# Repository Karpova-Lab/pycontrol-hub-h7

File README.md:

- [Documentation](https://karpova-lab.github.io/pycontrol-hub-h7/)
- [Development discussion](https://github.com/orgs/pyControl/discussions/171)

# pyControl Hub H7

A high-performance hardware hub for [pyControl](https://pycontrol.readthedocs.io/en/latest/), built around an [STM32H743VIT6](https://www.digikey.com/short/4cmvhp93) microcontroller. It interfaces with pyControl [devices](https://pycontrol.readthedocs.io/en/latest/user-guide/hardware/#devices) to record inputs and control outputs for behavioral experiments.

## Features

- 480 MHz Cortex-M7, 1 MB RAM, 2 MB external QSPI flash
- 11 pyControl behavior ports
  - 10 RJ45 connectors
  - 1 auxiliary [8-position terminal block](https://www.digikey.com/short/fpqf2rj0) that pairs with a [screw terminal plug](https://www.digikey.com/short/n57m4m7h)
- 2 BNC connectors
- 1 I²C connector compatible with [Qwiic](https://www.sparkfun.com/qwiic) / [STEMMA QT](https://learn.adafruit.com/introducing-adafruit-stemma-qt/what-is-stemma-qt) / [Qw/ST](https://shop.pimoroni.com/en-us/collections/breakouts?tags=Qw/ST) / [Modulino](https://store.arduino.cc/collections/modulino)
- USB Type-C connector with ESD protection
- DC barrel jack input with reverse polarity protection
- On/off toggle switch, 4 user buttons, reset button, and a DFU button for bootloader access
- Power and USB indicator LEDs, plus 4 user-controllable LEDs (red, yellow, green, blue)
- [Metal enclosure](https://karpova-lab.github.io/pycontrol-hub-h7/building/#case)
- Mounting holes compatible with [DIN rail adapters](https://www.digikey.com/short/h7977mfv) for securing to a [DIN rail](https://www.digikey.com/en/products/filter/hardware-fasteners-accessories/580?s=N4IgjCBcpgHAzFUBjKAzAhgGwM4FMAaEAeygG0QAWMeWSgThAF0iAHAFyhAGV2AnAJYA7AOYgAvkQC0AJiQhUkfgFdCJciACszcZJBzIFACIBJAHIACPhgFYQRU5eu2dQA). Alternatively, the case can sit on [rubber feet](https://www.mcmaster.com/9377k311/).

See the [board comparison](https://karpova-lab.github.io/pycontrol-hub-h7/#pycontrol-board-comparison) for how it stacks up against the pyControl Breakout 1.2.

## Photos

## Peripherals and pin mapping

## Schematic

## Repository layout

| Path | Contents |
|------|----------|
| [`ecad/`](ecad) | KiCad schematic and PCB, BOMs, and Gerbers |
| [`mcad/`](mcad) | Enclosure (laser-cut panels, STEP models) and 3D-printed standoffs |
| [`zensical/`](zensical) | Documentation source |
| [`docs/`](docs) | Built documentation site, served by GitHub Pages |

The KiCad libraries in `ecad/libs` are a git submodule, so clone recursively:

```sh
git clone --recursive https://github.com/Karpova-Lab/pycontrol-hub-h7.git
```

## License

- Hardware designs: [Janelia Open-Source Hardware license](LICENSE_HW.txt)
- Software: [BSD 3-Clause license](LICENSE_SW.txt)

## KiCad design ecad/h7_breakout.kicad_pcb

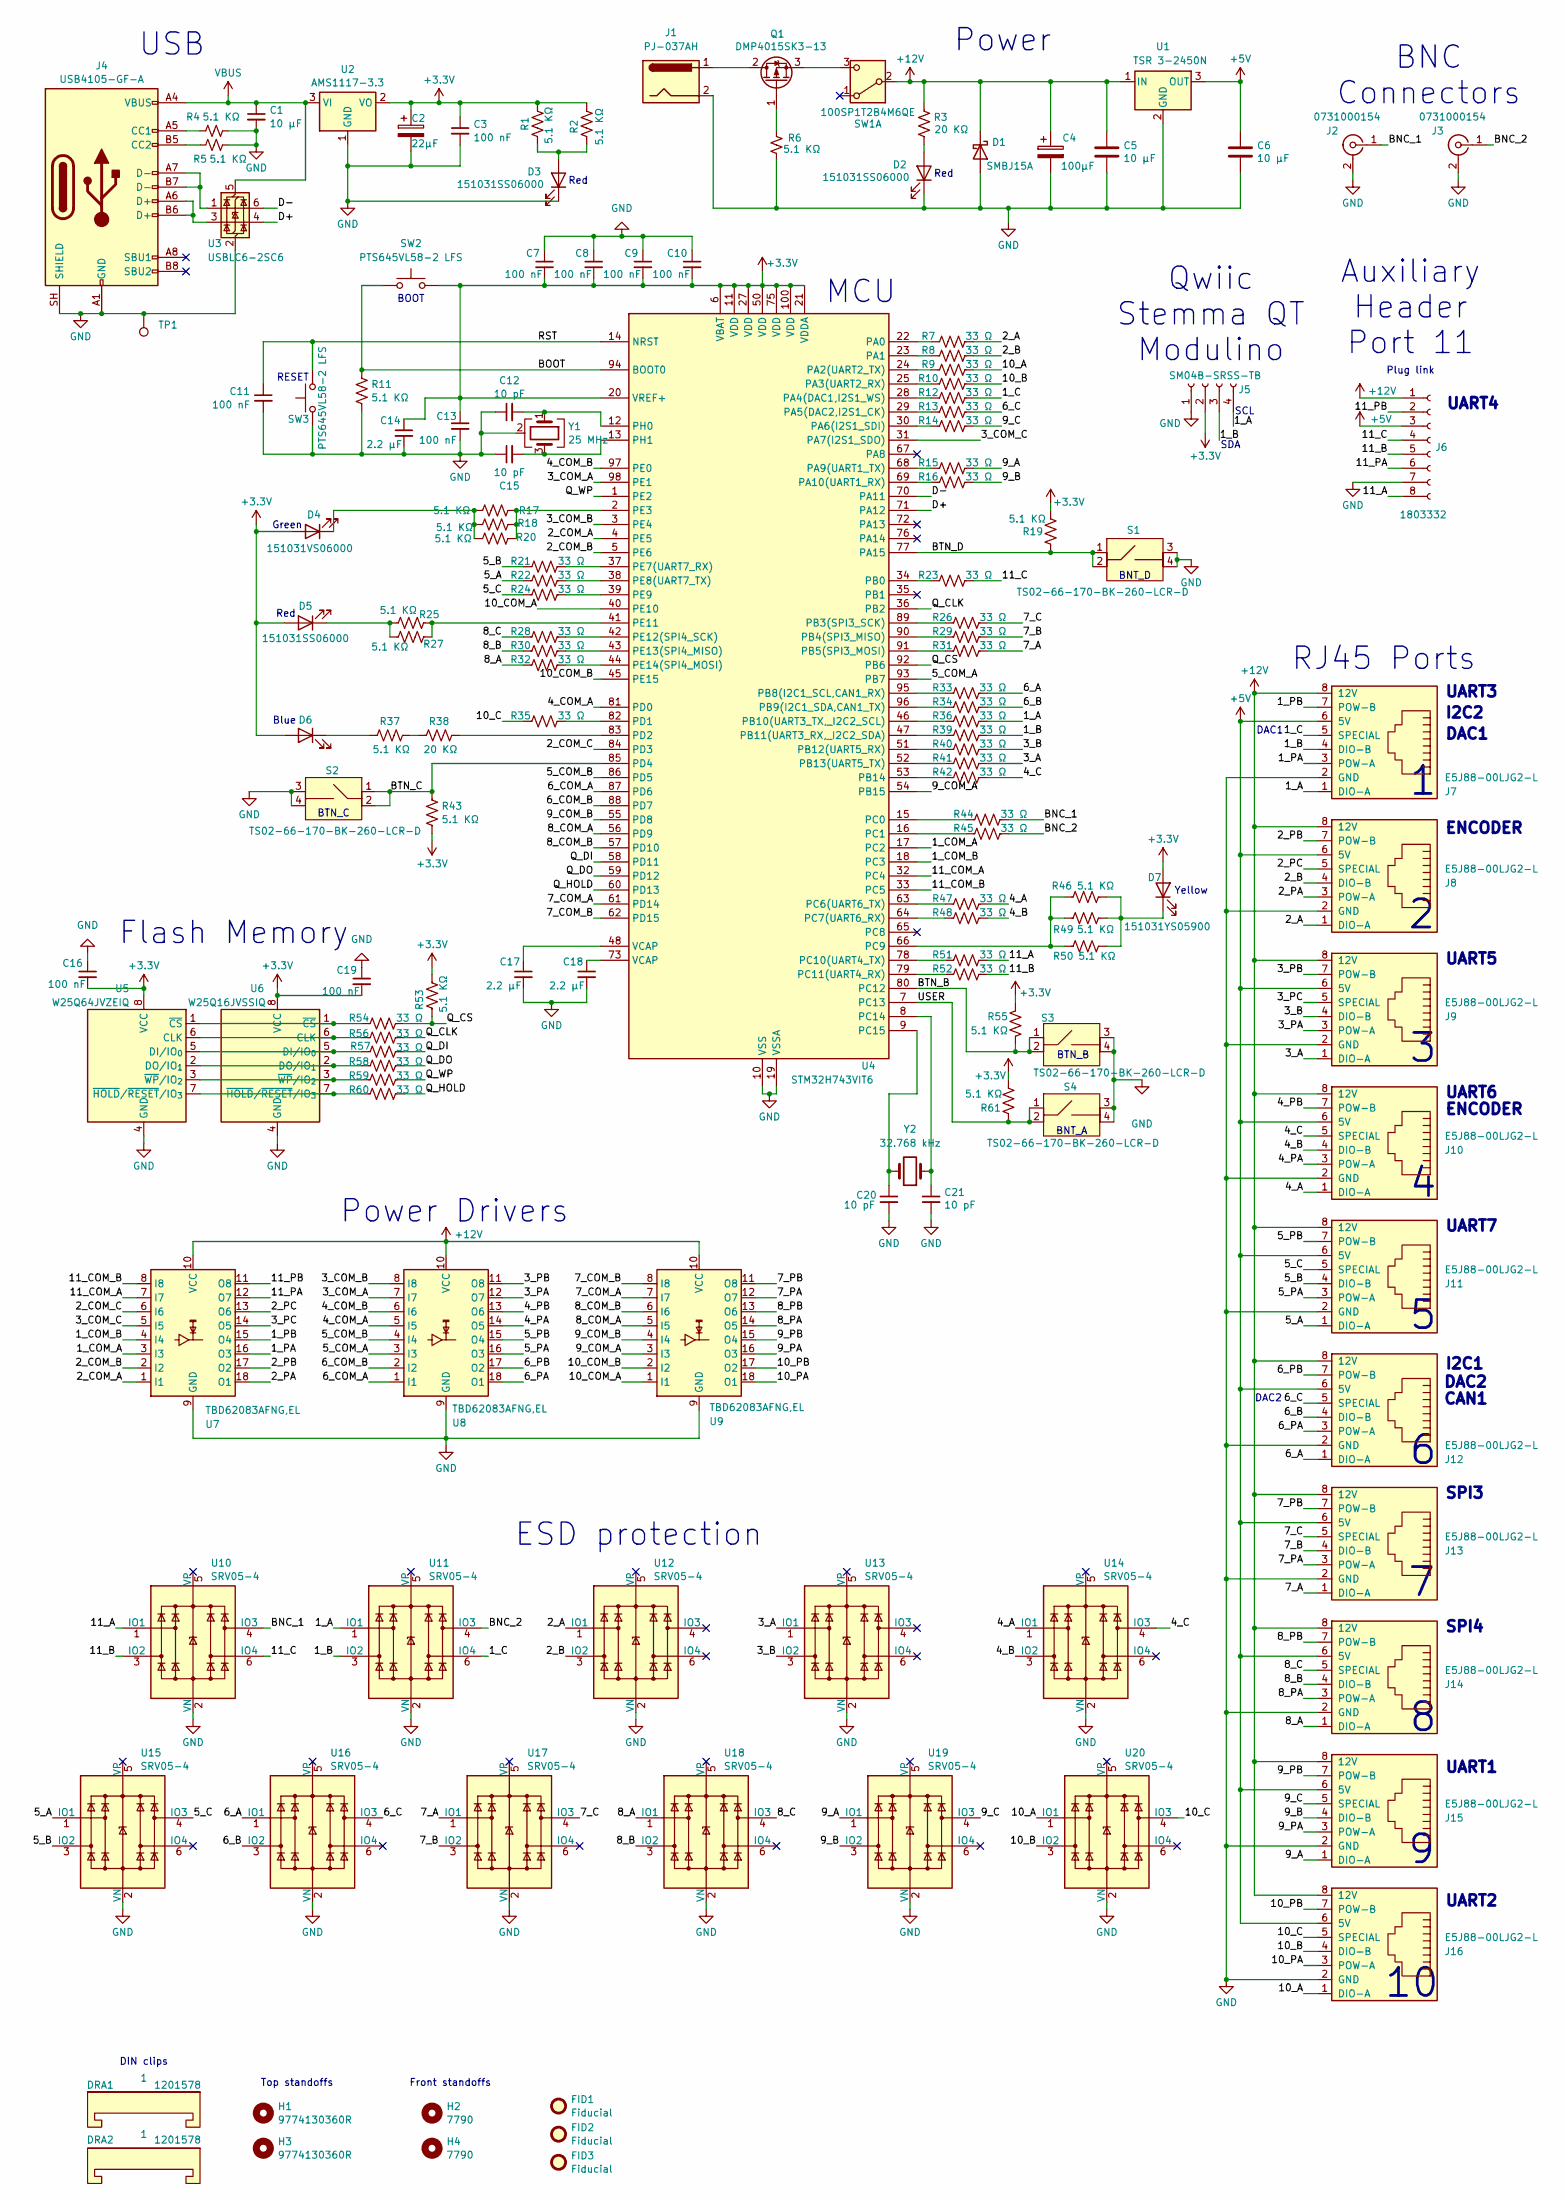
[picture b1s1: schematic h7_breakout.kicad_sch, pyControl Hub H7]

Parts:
C1, C5, C6: 10 µF; C_1206_3216Metric_Pad1.33x1.80mm_HandSolder
C2: 22µF; CP_EIA-3528-21_Kemet-B_HandSolder
C3, C7, C8, C9, C10, C11, C13, C16, C19: 100 nF; C_0603_1608Metric_Pad1.08x0.95mm_HandSolder
C4: 100µF; C_Elec_8x10.2
C12, C15, C20, C21: 10 pF; C_0603_1608Metric_Pad1.08x0.95mm_HandSolder
C14, C17, C18: 2.2 µF; C_0603_1608Metric_Pad1.08x0.95mm_HandSolder
D1: SMBJ15A; D_SMB
D2, D3, D5: 151031SS06000; LED_D3.0mm
D4: 151031VS06000; LED_D3.0mm
D6: 151033BS03000; LED_D3.0mm
D7: 151031YS05900; LED_D3.0mm
DRA1, DRA2: 1201578; DIN_Clip
FID1, FID2, FID3: Fiducial; Fiducial_0.75mm_Mask2.25mm
H1, H3: 9774130360R; standoff_13mm
H2, H4: 7790; RA_screw_mount
J1: PJ-037AH; DC_Jack
J2, J3: 0731000154; BNC RA Jack
J4: USB4105-GF-A; USB_C_Receptacle_GCT_USB4105-xx-A_16P_TopMnt_Horizontal
J5: SM04B-SRSS-TB; JST_SH_SM04B-SRSS-TB_1x04-1MP_P1.00mm_Horizontal
J6: 1803332; PhoenixContact_MC_1,5_8-G-3.81_1x08_P3.81mm_Horizontal
J7, J8, J9, J10, J11, J12, J13, J14, J15, J16: E5J88-00LJG2-L; RJ45_THP_tab_on_top
Q1: DMP4015SK3-13; TO-252-2
R1, R2, R4, R5, R6, R11, R17, R18, R19, R20, R25, R27, R37, R43, R46, R49, R50, R53, R55, R61: 5.1 KΩ; R_0603_1608Metric_Pad0.98x0.95mm_HandSolder
R3, R38: 20 KΩ; R_0603_1608Metric_Pad0.98x0.95mm_HandSolder
R7, R8, R9, R10, R12, R13, R14, R15, R16, R21, R22, R23, R24, R26, R28, R29, R30, R31, R32, R33, R34, R35, R36, R39, R40, R41, R42, R44, R45, R47, R48, R51, R52, R54, R56, R57, R58, R59, R60: 33 Ω; R_0603_1608Metric_Pad0.98x0.95mm_HandSolder
S1, S2, S3, S4: TS02-66-170-BK-260-LCR-D; SW_TH_Tactile_TS02-66-170
SW1: 100SP1T2B4M6QE; RA toggle
SW2, SW3: PTS645VL58-2 LFS; SW_Tactile_SPST_Angled_PTS645Vx58-2LFS
TP1: TestPoint_THTPad_D2.0mm_Drill1.0mm
U1: TSR 3-2450N; Converter_DCDC_traco_3A
U2: AMS1117-3.3; SOT-223-3_TabPin2
U3: USBLC6-2SC6; SOT-23-6; LCSC C7519
U4: STM32H743VIT6; LQFP-100_14x14mm_P0.5mm; LCSC C114409
U5: W25Q64JVZEIQ; WSON-8-1EP_8x6mm_P1.27mm_EP3.4x4.3mm; LCSC C97522
U6: W25Q16JVSSIQ; SOIC-8_5.3x5.3mm_P1.27mm
U7, U8, U9: TBD62083AFNG,EL; SSOP-18_4.4x6.5mm_P0.65mm; LCSC C163229
U10, U11, U12, U13, U14, U15, U16, U17, U18, U19, U20: SRV05-4; SOT-23-6; LCSC C460588
Y1: 25 MHz; crystal_STDCRS2-25M
Y2: 32.768 kHz; Crystal_SMD_EuroQuartz_EQ161-2Pin_3.2x1.5mm_HandSoldering

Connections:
+5V: C6.1, J6.3, J7.6 (5V), J8.6 (5V), J9.6 (5V), J10.6 (5V), J11.6 (5V), J12.6 (5V), J13.6 (5V), J14.6 (5V), J15.6 (5V), J16.6 (5V), U1.3 (OUT)
+12V: C4.1, C5.1, D1.1 (K), J6.1, J7.8 (12V), J8.8 (12V), J9.8 (12V), J10.8 (12V), J11.8 (12V), J12.8 (12V), J13.8 (12V), J14.8 (12V), J15.8 (12V), J16.8 (12V), R3.1, SW1.2 (B), U1.1 (IN), U7.10 (VCC), U8.10 (VCC), U9.10 (VCC)
/1_A: J5.4, J7.1 (DIO-A), R36.2, U11.1 (IO1)
/1_B: J5.3, J7.4 (DIO-B), R39.2, U11.3 (IO2)
/1_C: J7.5 (SPECIAL), R12.2, U11.6 (IO4)
/1_COM_A: U4.17 (PC2), U7.3 (I3)
/1_COM_B: U4.18 (PC3), U7.4 (I4)
/1_PA: J7.3 (POW-A), U7.16 (O3)
/1_PB: J7.7 (POW-B), U7.15 (O4)
/2_A: J8.1 (DIO-A), R7.2, U12.1 (IO1)
/2_B: J8.4 (DIO-B), R8.2, U12.3 (IO2)
/2_COM_A: U4.4 (PE5), U7.1 (I1)
/2_COM_B: U4.5 (PE6), U7.2 (I2)
/2_COM_C: U4.84 (PD3), U7.6 (I6)
/2_PA: J8.3 (POW-A), U7.18 (O1)
/2_PB: J8.7 (POW-B), U7.17 (O2)
/2_PC: J8.5 (SPECIAL), U7.13 (O6)
/3_A: J9.1 (DIO-A), R41.2, U13.1 (IO1)
/3_B: J9.4 (DIO-B), R40.2, U13.3 (IO2)
/3_COM_A: U4.98 (PE1), U8.7 (I7)
/3_COM_B: U4.3 (PE4), U8.8 (I8)
/3_COM_C: U4.31 (PA7(I2S1_SDO)), U7.5 (I5)
/3_PA: J9.3 (POW-A), U8.12 (O7)
/3_PB: J9.7 (POW-B), U8.11 (O8)
/3_PC: J9.5 (SPECIAL), U7.14 (O5)
/4_A: J10.1 (DIO-A), R47.2, U14.1 (IO1)
/4_B: J10.4 (DIO-B), R48.2, U14.3 (IO2)
/4_C: J10.5 (SPECIAL), R42.2, U14.4 (IO3)
/4_COM_A: U4.81 (PD0), U8.5 (I5)
/4_COM_B: U4.97 (PE0), U8.6 (I6)
/4_PA: J10.3 (POW-A), U8.14 (O5)
/4_PB: J10.7 (POW-B), U8.13 (O6)
/5_A: J11.1 (DIO-A), R22.1, U15.1 (IO1)
/5_B: J11.4 (DIO-B), R21.1, U15.3 (IO2)
/5_C: J11.5 (SPECIAL), R24.1, U15.4 (IO3)
/5_COM_A: U4.93 (PB7), U8.3 (I3)
/5_COM_B: U4.86 (PD5), U8.4 (I4)
/5_PA: J11.3 (POW-A), U8.16 (O3)
/5_PB: J11.7 (POW-B), U8.15 (O4)
/6_A: J12.1 (DIO-A), R33.2, U16.1 (IO1)
/6_B: J12.4 (DIO-B), R34.2, U16.3 (IO2)
/6_C: J12.5 (SPECIAL), R13.2, U16.4 (IO3)
/6_COM_A: U4.87 (PD6), U8.1 (I1)
/6_COM_B: U4.88 (PD7), U8.2 (I2)
/6_PA: J12.3 (POW-A), U8.18 (O1)
/6_PB: J12.7 (POW-B), U8.17 (O2)
/7_A: J13.1 (DIO-A), R31.2, U17.1 (IO1)
/7_B: J13.4 (DIO-B), R29.2, U17.3 (IO2)
/7_C: J13.5 (SPECIAL), R26.2, U17.4 (IO3)
/7_COM_A: U4.61 (PD14), U9.7 (I7)
/7_COM_B: U4.62 (PD15), U9.8 (I8)
/7_PA: J13.3 (POW-A), U9.12 (O7)
/7_PB: J13.7 (POW-B), U9.11 (O8)
/8_A: J14.1 (DIO-A), R32.1, U18.1 (IO1)
/8_B: J14.4 (DIO-B), R30.1, U18.3 (IO2)
/8_C: J14.5 (SPECIAL), R28.1, U18.4 (IO3)
/8_COM_A: U4.56 (PD9), U9.5 (I5)
/8_COM_B: U4.57 (PD10), U9.6 (I6)
/8_PA: J14.3 (POW-A), U9.14 (O5)
/8_PB: J14.7 (POW-B), U9.13 (O6)
/9_A: J15.1 (DIO-A), R15.2, U19.1 (IO1)
/9_B: J15.4 (DIO-B), R16.2, U19.3 (IO2)
/9_C: J15.5 (SPECIAL), R14.2, U19.4 (IO3)
/9_COM_A: U4.54 (PB15), U9.3 (I3)
/9_COM_B: U4.55 (PD8), U9.4 (I4)
/9_PA: J15.3 (POW-A), U9.16 (O3)
/9_PB: J15.7 (POW-B), U9.15 (O4)
/10_A: J16.1 (DIO-A), R9.2, U20.1 (IO1)
/10_B: J16.4 (DIO-B), R10.2, U20.3 (IO2)
/10_C: J16.5 (SPECIAL), R35.1, U20.4 (IO3)
/10_COM_A: U4.40 (PE10), U9.1 (I1)
/10_COM_B: U4.45 (PE15), U9.2 (I2)
/10_PA: J16.3 (POW-A), U9.18 (O1)
/10_PB: J16.7 (POW-B), U9.17 (O2)
/11_A: J6.8, R51.2, U10.1 (IO1)
/11_B: J6.5, R52.2, U10.3 (IO2)
/11_C: J6.4, R23.2, U10.6 (IO4)
/11_COM_A: U4.32 (PC4), U7.7 (I7)
/11_COM_B: U4.33 (PC5), U7.8 (I8)
/11_PA: J6.6, U7.12 (O7)
/11_PB: J6.2, U7.11 (O8)
/BNC_1: J2.1 (In), R44.2, U10.4 (IO3)
/BNC_2: J3.1 (In), R45.2, U11.4 (IO3)
/BTN_B: R55.1, S3.1 (in1), S3.2 (in2), U4.80 (PC12)
/BTN_C: R43.2, S2.1 (in1), S2.2 (in2), U4.85 (PD4)
/BTN_D: R19.2, S1.1 (in1), S1.2 (in2), U4.77 (PA15)
/D+: U3.4 (I/O2), U4.71 (PA12)
/D-: U3.6 (I/O1), U4.70 (PA11)
/Q_CLK: R56.2, U4.36 (PB2)
/Q_CS: R53.2, R54.2, U4.92 (PB6)
/Q_DI: R57.2, U4.58 (PD11)
/Q_DO: R58.2, U4.59 (PD12)
/Q_HOLD: R60.2, U4.60 (PD13)
/Q_WP: R59.2, U4.1 (PE2)
/USER: R61.2, S4.1 (in1), S4.2 (in2), U4.7 (PC13)
unnamed: C17.1, U4.48 (VCAP)
unnamed: C18.1, U4.73 (VCAP)
unnamed: D2.2 (A), R3.2
unnamed: D3.2 (A), R1.2, R2.2
unnamed: D4.1 (K), R17.1, R18.1, R20.1
unnamed: D5.1 (K), R25.1, R27.1
unnamed: D6.1 (K), R37.1
unnamed: D7.1 (K), R46.2, R49.2, R50.2
unnamed: J4.A5 (CC1), R4.1
unnamed: J4.B5 (CC2), R5.2
unnamed: J4.A6 (D+), J4.B6 (D+), U3.3 (I/O2)
unnamed: J4.A7 (D-), J4.B7 (D-), U3.1 (I/O1)
unnamed: J1.1, Q1.2 (D)
unnamed: Q1.1 (G), R6.1
unnamed: Q1.3 (S), SW1.3 (C)
unnamed: R37.2, R38.1
unnamed: R7.1, U4.22 (PA0)
unnamed: R8.1, U4.23 (PA1)
unnamed: R9.1, U4.24 (PA2(UART2_TX))
unnamed: R10.1, U4.25 (PA3(UART2_RX))
unnamed: R12.1, U4.28 (PA4(DAC1,I2S1_WS))
unnamed: R13.1, U4.29 (PA5(DAC2,I2S1_CK))
unnamed: R14.1, U4.30 (PA6(I2S1_SDI))
unnamed: R15.1, U4.68 (PA9(UART1_TX))
unnamed: R16.1, U4.69 (PA10(UART1_RX))
unnamed: R23.1, U4.34 (PB0)
unnamed: R26.1, U4.89 (PB3(SPI3_SCK))
unnamed: R29.1, U4.90 (PB4(SPI3_MISO))
unnamed: R31.1, U4.91 (PB5(SPI3_MOSI))
unnamed: R33.1, U4.95 (PB8(I2C1_SCL,CAN1_RX))
unnamed: R34.1, U4.96 (PB9(I2C1_SDA,CAN1_TX))
unnamed: R36.1, U4.46 (PB10(UART3_TX,_I2C2_SCL))
unnamed: R39.1, U4.47 (PB11(UART3_RX,_I2C2_SDA))
unnamed: R40.1, U4.51 (PB12(UART5_RX))
unnamed: R41.1, U4.52 (PB13(UART5_TX))
unnamed: R42.1, U4.53 (PB14)
unnamed: R44.1, U4.15 (PC0)
unnamed: R45.1, U4.16 (PC1)
unnamed: R47.1, U4.63 (PC6(UART6_TX))
unnamed: R48.1, U4.64 (PC7(UART6_RX))
unnamed: R46.1, R49.1, R50.1, U4.66 (PC9)
unnamed: R51.1, U4.78 (PC10(UART4_TX))
unnamed: R52.1, U4.79 (PC11(UART4_RX))
unnamed: C21.1, U4.8 (PC14), Y2.1
unnamed: C20.1, U4.9 (PC15), Y2.2
unnamed: R35.2, U4.82 (PD1)
unnamed: R38.2, U4.83 (PD2)
unnamed: R17.2, R18.2, R20.2, U4.2 (PE3)
unnamed: R21.2, U4.37 (PE7(UART7_RX))
unnamed: R22.2, U4.38 (PE8(UART7_TX))
unnamed: R24.2, U4.39 (PE9)
unnamed: R25.2, R27.2, U4.41 (PE11)
unnamed: R28.2, U4.42 (PE12(SPI4_SCK))
unnamed: R30.2, U4.43 (PE13(SPI4_MISO))
unnamed: R32.2, U4.44 (PE14(SPI4_MOSI))
unnamed: C12.2, U4.12 (PH0), Y1.1
unnamed: C15.2, U4.13 (PH1), Y1.3
unnamed: R56.1, U5.6 (CLK), U6.6 (CLK)
unnamed: R57.1, U5.5 (DI/IO_{0}), U6.5 (DI/IO_{0})
unnamed: R58.1, U5.2 (DO/IO_{1}), U6.2 (DO/IO_{1})
unnamed: R54.1, U5.1 (~CS), U6.1 (~CS)
unnamed: R60.1, U5.7 (~HOLD/~RESET/IO_{3}), U6.7 (~HOLD/~RESET/IO_{3})
unnamed: R59.1, U5.3 (~WP/IO_{2}), U6.3 (~WP/IO_{2})
VBUS: C1.1, J4.A4 (VBUS), J4.A9 (VBUS), J4.B4 (VBUS), J4.B9 (VBUS), U2.3 (VI), U3.5 (VBUS)

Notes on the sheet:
SDA
DAC2
I2C2
UART4
Plug link
Power Drivers
Auxiliary Header Port 11
ESD protection
DIN clips
ENCODER
BOOT
USB
Red
SPI4
Qwiic Stemma QT Modulino
I2C1
BTN_B
RJ45 Ports
BNT_D
SCL
Flash Memory
BNT_A
DAC1
UART6
SPI3
UART1
UART3
Blue
UART7
UART2
RESET
Green
Front standoffs
BNC Connectors
UART5
Power
Yellow
CAN1
BTN_C
MCU

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
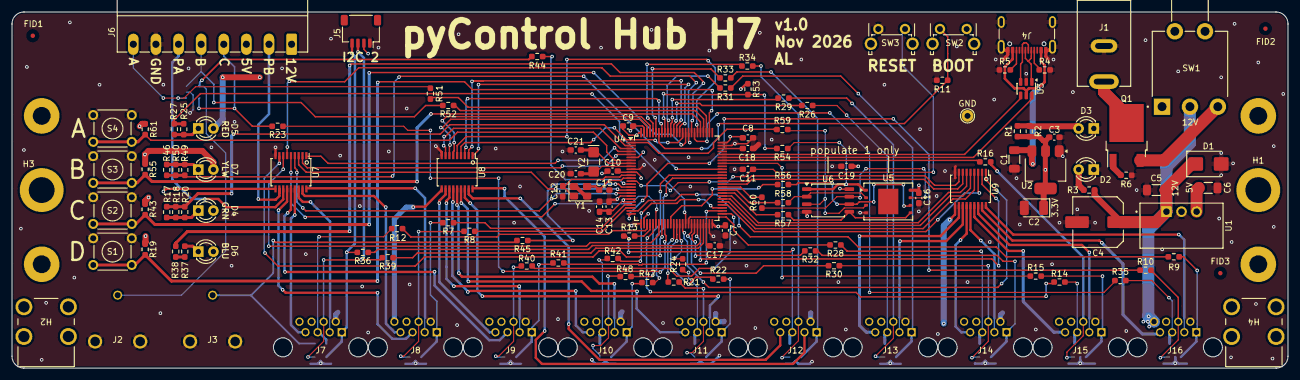
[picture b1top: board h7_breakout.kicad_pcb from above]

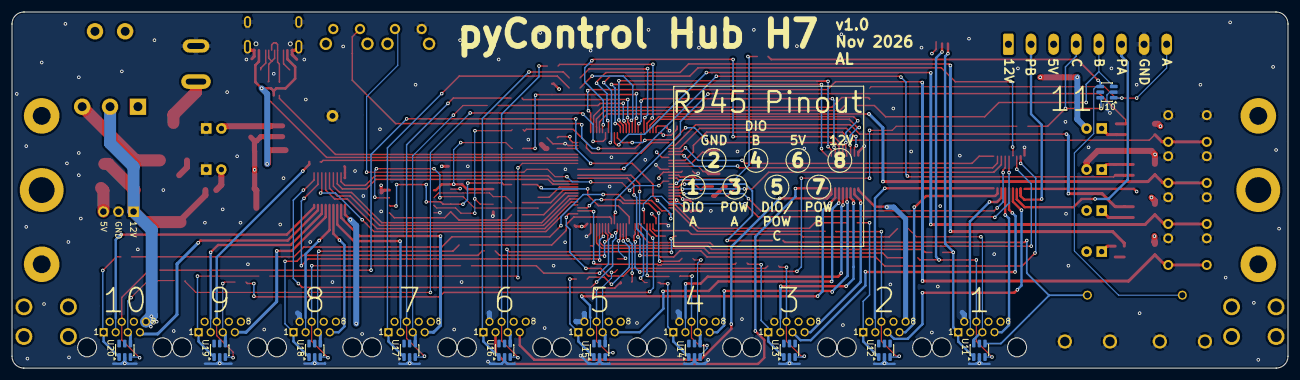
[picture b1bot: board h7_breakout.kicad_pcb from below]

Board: 4 copper layers, 215.0 x 60.0 mm, 145 parts (11 on the bottom side), 163 nets.
